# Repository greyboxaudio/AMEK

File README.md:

# AMEK
 
A collection of files & circuits for AMEK desks

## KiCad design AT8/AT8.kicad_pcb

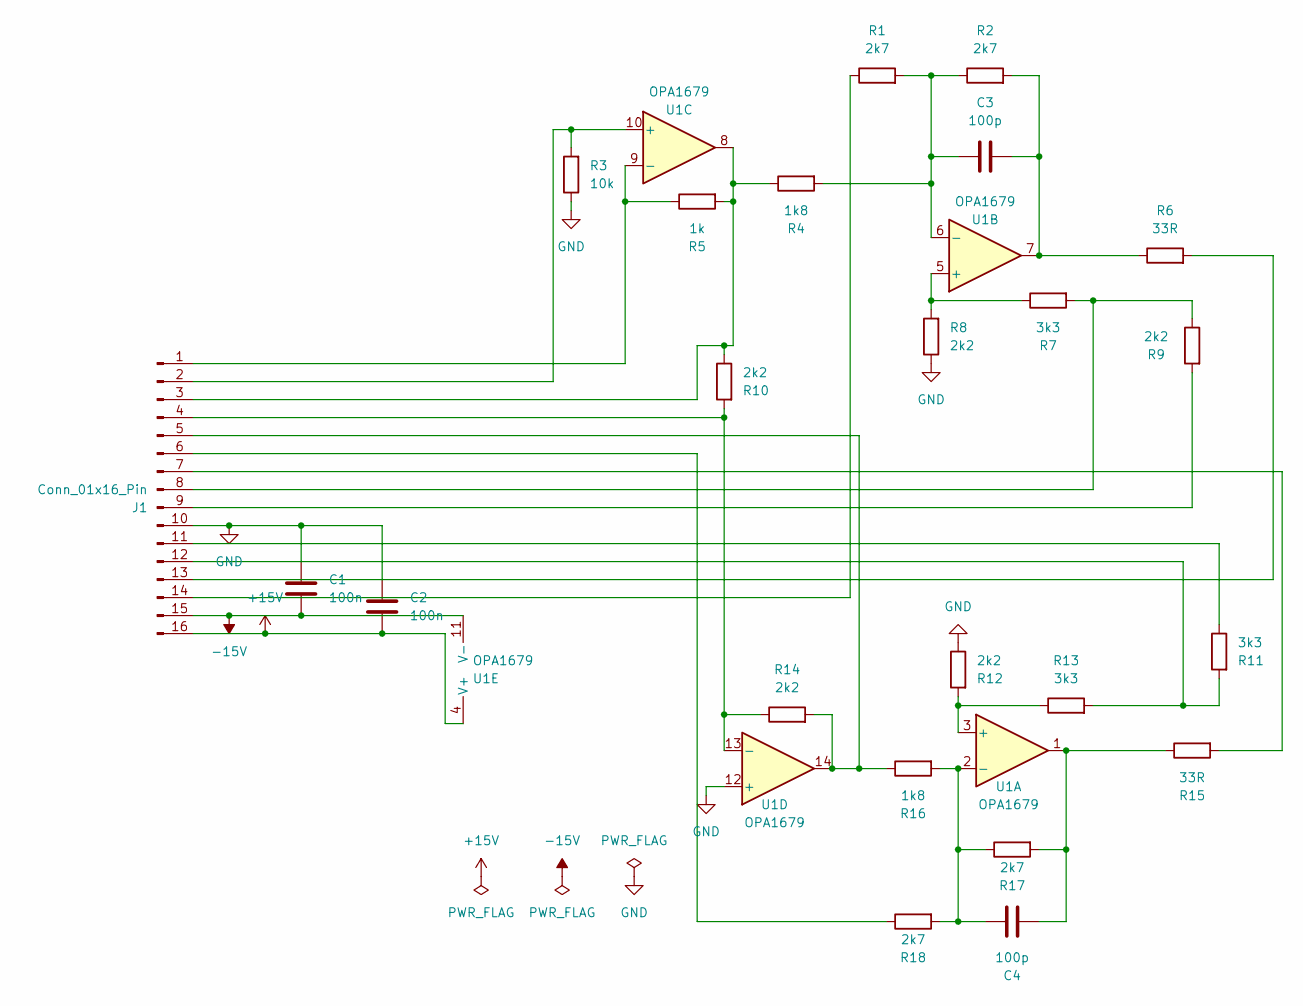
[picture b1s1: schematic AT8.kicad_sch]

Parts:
C1, C2: 100n; C_0805_2012Metric
C3, C4: 100p; C_0805_2012Metric
J1: Conn_01x16_Pin; PinHeader_1x16_P2.54mm_Horizontal
R1, R2, R17, R18: 2k7; R_0805_2012Metric
R3: 10k; R_0805_2012Metric
R4, R16: 1k8; R_0805_2012Metric
R5: 1k; R_0805_2012Metric
R6, R15: 33R; R_0805_2012Metric
R7, R11, R13: 3k3; R_0805_2012Metric
R8, R9, R10, R12, R14: 2k2; R_0805_2012Metric
U1: OPA1679; SOIC-14_3.9x8.7mm_P1.27mm

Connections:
+15V: C2.1, J1.16, U1.4 (V+)
-15V: C1.1, J1.15, U1.11 (V-)
GND: C1.2, C2.2, J1.10, R3.1, R8.1, R12.1, U1.12 (+)
unnamed: C3.2, R2.2, R6.1, U1.7
unnamed: C4.2, R15.1, R17.2, U1.1
unnamed: J1.1, R5.1, U1.9 (-)
unnamed: J1.2, R3.2, U1.10 (+)
unnamed: J1.3, R4.1, R5.2, R10.1, U1.8
unnamed: J1.4, R10.2, R14.1, U1.13 (-)
unnamed: J1.5, R14.2, R16.1, U1.14
unnamed: J1.6, R18.1
unnamed: J1.7, R15.2
unnamed: J1.8, R7.2, R9.1
unnamed: J1.9, R9.2
unnamed: J1.11, R11.1
unnamed: J1.12, R11.2, R13.2
unnamed: J1.13, R6.2
unnamed: J1.14, R1.1
unnamed: R12.2, R13.1, U1.3 (+)
unnamed: C4.1, R16.2, R17.1, R18.2, U1.2 (-)
unnamed: R7.1, R8.2, U1.5 (+)
unnamed: C3.1, R1.2, R2.1, R4.2, U1.6 (-)

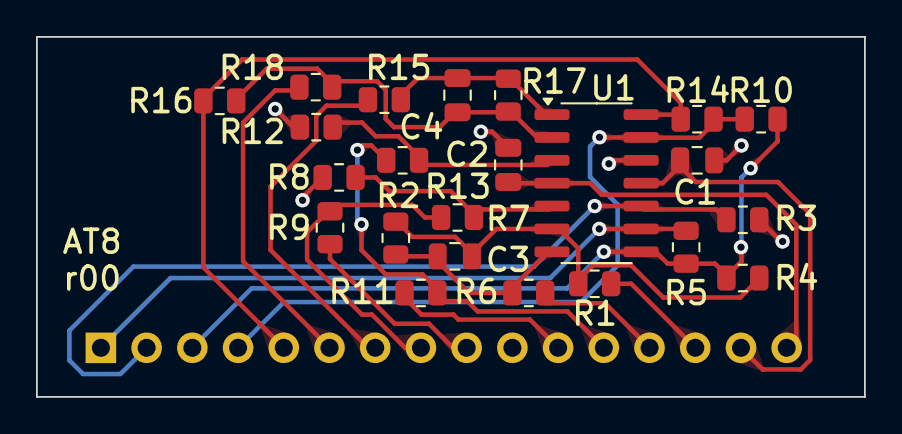
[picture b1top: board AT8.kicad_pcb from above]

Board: 2 copper layers, 46.0 x 20.0 mm, 24 parts (1 on the bottom side), 22 nets.

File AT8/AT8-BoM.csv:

"Reference","Value","Datasheet","Footprint","Qty","DNP"
"C1,C2","100n","~","Capacitor_SMD:C_0805_2012Metric","2",""
"C3,C4","100p","~","Capacitor_SMD:C_0805_2012Metric","2",""
"J1","Conn_01x16_Pin","~","Connector_PinHeader_2.54mm:PinHeader_1x16_P2.54mm_Horizontal","1",""
"R1,R2,R17,R18","2k7","~","Resistor_SMD:R_0805_2012Metric","4",""
"R3","10k","~","Resistor_SMD:R_0805_2012Metric","1",""
"R4,R16","1k8","~","Resistor_SMD:R_0805_2012Metric","2",""
"R5","1k","~","Resistor_SMD:R_0805_2012Metric","1",""
"R6,R15","33R","~","Resistor_SMD:R_0805_2012Metric","2",""
"R7,R11,R13","3k3","~","Resistor_SMD:R_0805_2012Metric","3",""
"R8,R9,R10,R12,R14","2k2","~","Resistor_SMD:R_0805_2012Metric","5",""
"U1","OPA1679","http://www.ti.com/lit/ds/symlink/opa1678.pdf","Package_SO:SOIC-14_3.9x8.7mm_P1.27mm","1",""
